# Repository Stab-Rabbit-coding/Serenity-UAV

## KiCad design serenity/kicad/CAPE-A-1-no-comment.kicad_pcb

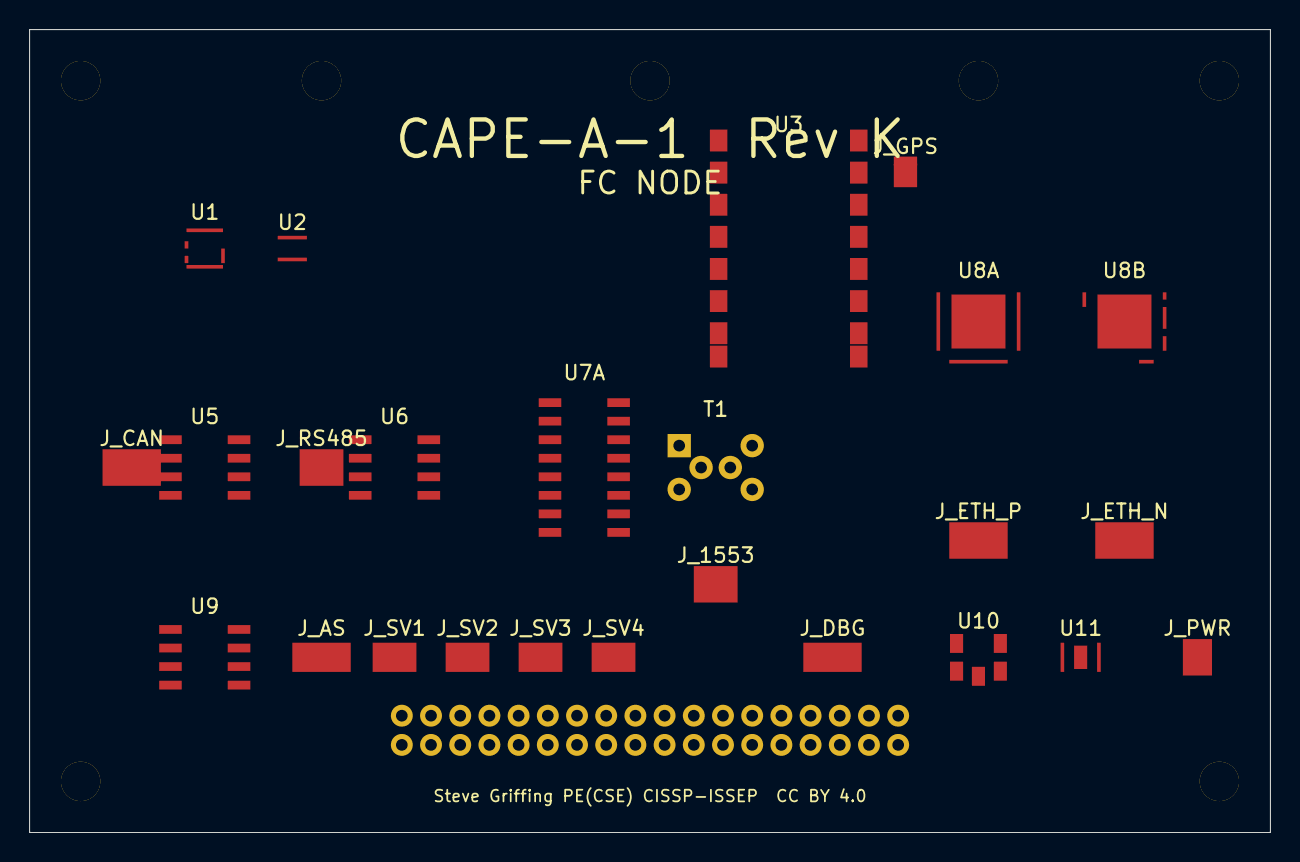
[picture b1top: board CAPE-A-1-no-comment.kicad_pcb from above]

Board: 4 copper layers, 85.0 x 55.0 mm, 25 parts (0 on the bottom side), 25 nets, no tracks yet.

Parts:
J_1553: JST_GH_SM03B-GHS-TB_1x03-1MM_Horizontal
J_AS: JST_SH_SM04B-SRSS-TB_1x04-1MM_Horizontal
J_CAN: JST_GH_SM04B-GHS-TB_1x04-1MM_Horizontal
J_DBG: JST_SH_SM04B-SRSS-TB_1x04-1MM_Horizontal
J_ETH_N: JST_GH_SM04B-GHS-TB_1x04-1MM_Horizontal
J_ETH_P: JST_GH_SM04B-GHS-TB_1x04-1MM_Horizontal
J_GPS: U.FL_Hirose_U.FL-R-SMT-1_Vertical
J_PWR: JST_GH_SM02B-GHS-TB_1x02-1MM_Horizontal
J_RS485: JST_GH_SM03B-GHS-TB_1x03-1MM_Horizontal
J_SV1, J_SV2, J_SV3, J_SV4: JST_SH_SM03B-SRSS-TB_1x03-1MM_Horizontal
T1: PE-68515; Pulse_PE-68515
U1: ICM-42688-P; InvenSense_ICM-42688-P_LGA-14_3x3mm_P0.5mm
U2: BMP388; Bosch_LGA-8_2x2mm_P0.5mm
U3: M10Q; u-blox_MAX-M10Q_LCC-16
U5: ATA6561; SOIC-8_3.9x4.9mm_P1.27mm
U6: MAX3485E; SOIC-8_3.9x4.9mm_P1.27mm
U7A: DS26LV31; SOIC-16_3.9x9.9mm_P1.27mm
U8A, U8B: DP83825I; QFN-32-1EP_5x5mm_P0.5mm_EP3.7x3.7mm
U9: SLB9670; SOIC-8_3.9x4.9mm_P1.27mm
U10: AP2112K-3.3; SOT-25_HandSoldering
U11: TPS62933; WSON-8-1EP_2x2mm_P0.5mm_EP0.9x1.6mm

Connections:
+3V3: J_AS.1, J_CAN.1, J_DBG.4, U1.5, U2.6, U2.8, U3.2, U5.8, U6.8, U7A.4, U7A.8, U7A.12, U7A.16, U8A.24, U8B.24, U9.8, U10.3, U10.5, U11.5, U11.6
+5V: J_PWR.1, J_SV1.1, J_SV2.1, J_SV3.1, J_SV4.1, U11.1, U11.2, U11.8
CANH: J_CAN.2, U5.6
CANL: J_CAN.3, U5.7
ETH_N_RX_N: J_ETH_N.4, U8B.22
ETH_N_RX_P: J_ETH_N.3, U8B.21
ETH_N_TX_N: J_ETH_N.2, U8B.18
ETH_N_TX_P: J_ETH_N.1, U8B.17
ETH_P_RX_N: J_ETH_P.4, U8A.22
ETH_P_RX_P: J_ETH_P.3, U8A.21
ETH_P_TX_N: J_ETH_P.2, U8A.18
ETH_P_TX_P: J_ETH_P.1, U8A.17
GND: J_1553.3, J_AS.2, J_CAN.4, J_DBG.1, J_GPS.2, J_PWR.2, J_RS485.3, J_SV1.2, J_SV2.2, J_SV3.2, J_SV4.2, U1.8, U1.9, U1.10, U1.11, U1.12, U1.14, U2.3, U2.5, U2.7, U3.1, U3.7, U3.8, U3.10, U3.11, U3.13, U3.14, U3.15, U3.16, U5.2, U5.5, U6.4, U7A.3, U7A.7, U7A.11, U7A.15, U8A.19, U8A.23, U8A.33, U8B.33, U9.2, U10.2, U11.3, U11.4, U11.7, U11.9
GPS_ANT_RF: J_GPS.1, U3.9
M1553_RX_N: T1.4, U7A.10
M1553_RX_P: T1.3, U7A.9
M1553_STUB_A: J_1553.1, T1.5
M1553_STUB_B: J_1553.2, T1.6
M1553_TX_N: T1.2, U7A.2
M1553_TX_P: T1.1, U7A.1
RS485_A: J_RS485.1, U6.5, U6.7
RS485_B: J_RS485.2, U6.6
RS485_DE: U6.2, U6.3
VDD_1V8_PHY: U8A.20, U8B.20
VSYS: U10.1, U10.4

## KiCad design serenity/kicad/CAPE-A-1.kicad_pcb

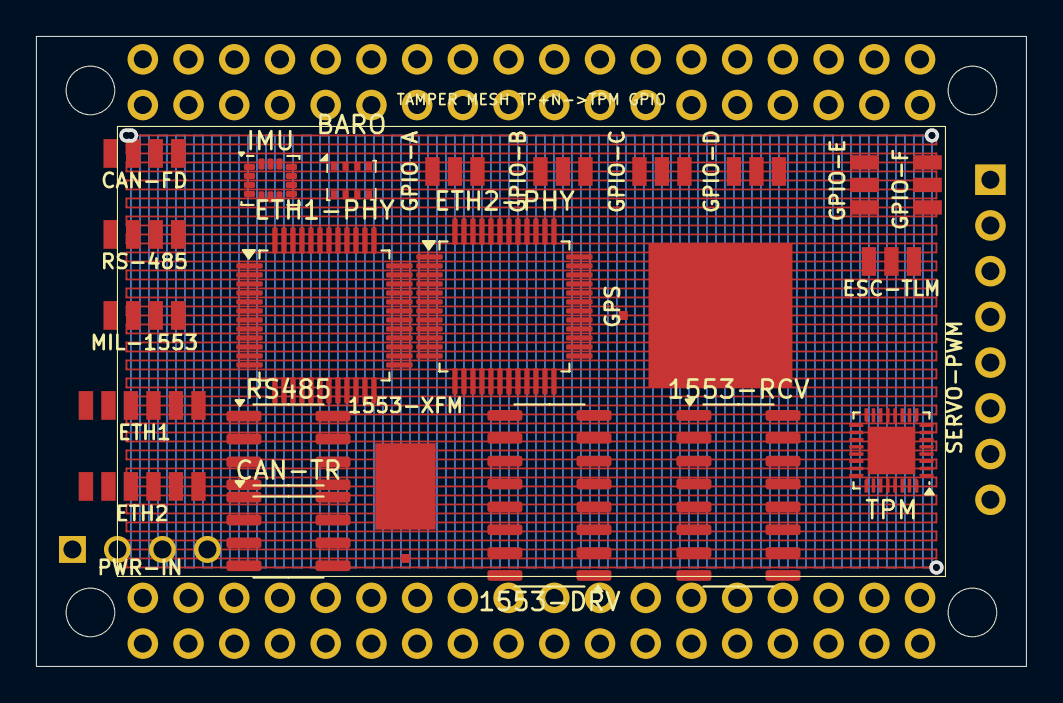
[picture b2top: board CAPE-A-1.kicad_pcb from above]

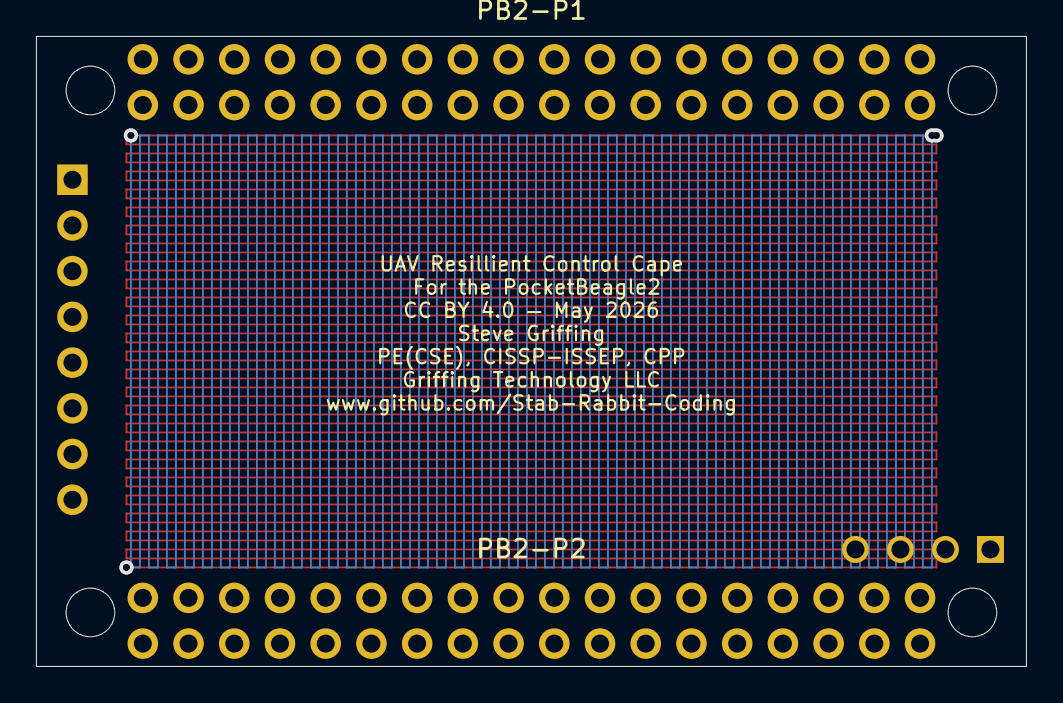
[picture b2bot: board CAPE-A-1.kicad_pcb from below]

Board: 4 copper layers, 55.0 x 35.0 mm, 27 parts (2 on the bottom side), 41 nets.

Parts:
1553-DRV: DS26LV31; SOIC-16_3.9x9.9mm_P1.27mm
1553-RCV: DS26LV32; SOIC-16_3.9x9.9mm_P1.27mm
1553-XFM: SM-1553-11; Package
BARO: BMP388; Bosch_LGA-8_2x2.5mm_P0.65mm_ClockwisePinNumbering
CAN-FD: JST-GH-4P-CAN; JST_GH_4P
CAN-TR: ATA6561; SOIC-8_3.9x4.9mm_P1.27mm
ESC-TLM: JST-GH-3P-ESC-TELEM; JST_GH_3P
ETH1: JST-GH-6P-ETH1; JST_GH_6P
ETH1-PHY, ETH2-PHY: DP83825I; LQFP-48_7x7mm_P0.5mm
ETH2: JST-GH-6P-ETH2; JST_GH_6P
GPIO-A: JST-GH-3P-GPIO; JST_GH_3P_V
GPIO-B: JST-GH-3P-GPIO; JST_GH_3P_V
GPIO-C: JST-GH-3P-GPIO; JST_GH_3P_V
GPIO-D: JST-GH-3P-GPIO; JST_GH_3P_V
GPIO-E: JST-GH-3P-GPIO; JST_GH_3P_V
GPIO-F: JST-GH-3P-GPIO; JST_GH_3P_V
GPS: SAM-M10Q-00B; Package
IMU: ICM-42688-P; LGA-14_3x2.5mm_P0.5mm_LayoutBorder3x4y
MIL-1553: JST-GH-4P-1553; JST_GH_4P
PB2-P1: PB2I-P1-2x18; 2x18_P1_Socket
PB2-P2: PB2I-P2-2x18; 2x18_P2_Socket
PWR-IN: Nano-Fit-4P-POWER; Connector_Molex_NanoFit
RS485: MAX3485E; SOIC-8_3.9x4.9mm_P1.27mm
RS-485: JST-GH-4P-RS485; JST_GH_4P
SERVO-PWM: 1x8-SERVO-PWM; Connector_PinHeader_2.54mm
TPM: SLB9670; QFN-32-1EP_4x4mm_P0.4mm_EP2.65x2.65mm

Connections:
+3V3: PB2-P1.33, PB2-P1.34
+5V: PB2-P1.35, PB2-P2.35
CAN_STB: CAN-TR.1, PB2-P1.14
GND: PB2-P1.1, PB2-P1.2, PB2-P1.36, PB2-P2.36
IMU_INT2: IMU.14, PB2-P1.18
MCAN0_RX: CAN-TR.3, PB2-P1.15
MCAN0_TX: CAN-TR.2, PB2-P1.16
MDC: ETH1-PHY.5, ETH2-PHY.5, PB2-P2.18
MDIO: ETH1-PHY.4, ETH2-PHY.4, PB2-P2.17
PHY1_INTRN: ETH1-PHY.3, PB2-P2.16
PHY1_RSTN: ETH1-PHY.2, PB2-P2.15
PHY2_INTRN: ETH2-PHY.3, PB2-P2.14
PHY2_RSTN: ETH2-PHY.2, PB2-P2.13
PRU_1553_RX_N: 1553-RCV.13, PB2-P1.7
PRU_1553_TX_N: 1553-DRV.6, PB2-P1.9
PRU_1553_TX_P: 1553-DRV.10, PB2-P1.10
RMII0_CRS_DV: ETH1-PHY.29, PB2-P2.29
RMII0_REF_CLK: ETH1-PHY.6, PB2-P2.27
RMII0_RXD1: ETH1-PHY.30, PB2-P2.30
RMII0_RX_ER: ETH1-PHY.28, PB2-P2.28
RMII0_TXD0: ETH1-PHY.37, PB2-P2.34
RMII0_TXD1: ETH1-PHY.32, PB2-P2.33
RMII0_TX_EN: ETH1-PHY.31, PB2-P2.32
RMII1_CRS_DV: ETH2-PHY.29, PB2-P2.21
RMII1_REF_CLK: ETH2-PHY.6, PB2-P2.19
RMII1_RXD1: ETH2-PHY.30, PB2-P2.22
RMII1_RX_ER: ETH2-PHY.28, PB2-P2.20
RMII1_TXD0: ETH2-PHY.37, PB2-P2.26
RMII1_TXD1: ETH2-PHY.32, PB2-P2.25
RMII1_TX_EN: ETH2-PHY.31, PB2-P2.24
RS485_DE: PB2-P1.11, RS485.2, RS485.4
RS485_RX: PB2-P1.12, RS485.5
RS485_TX: PB2-P1.13, RS485.3
SPI0_CLK: BARO.6, IMU.2, PB2-P1.25, TPM.23
SPI0_CS_BARO: BARO.7, PB2-P1.22
SPI0_CS_IMU: IMU.3, PB2-P1.26
SPI0_CS_TPM: PB2-P1.21, TPM.28
SPI0_MISO: BARO.3, IMU.5, PB2-P1.23, TPM.22
SPI0_MOSI: BARO.5, IMU.1, PB2-P1.24, TPM.21
TPM_IRQN: PB2-P2.12, TPM.24
TPM_RSTN: PB2-P2.11, TPM.1

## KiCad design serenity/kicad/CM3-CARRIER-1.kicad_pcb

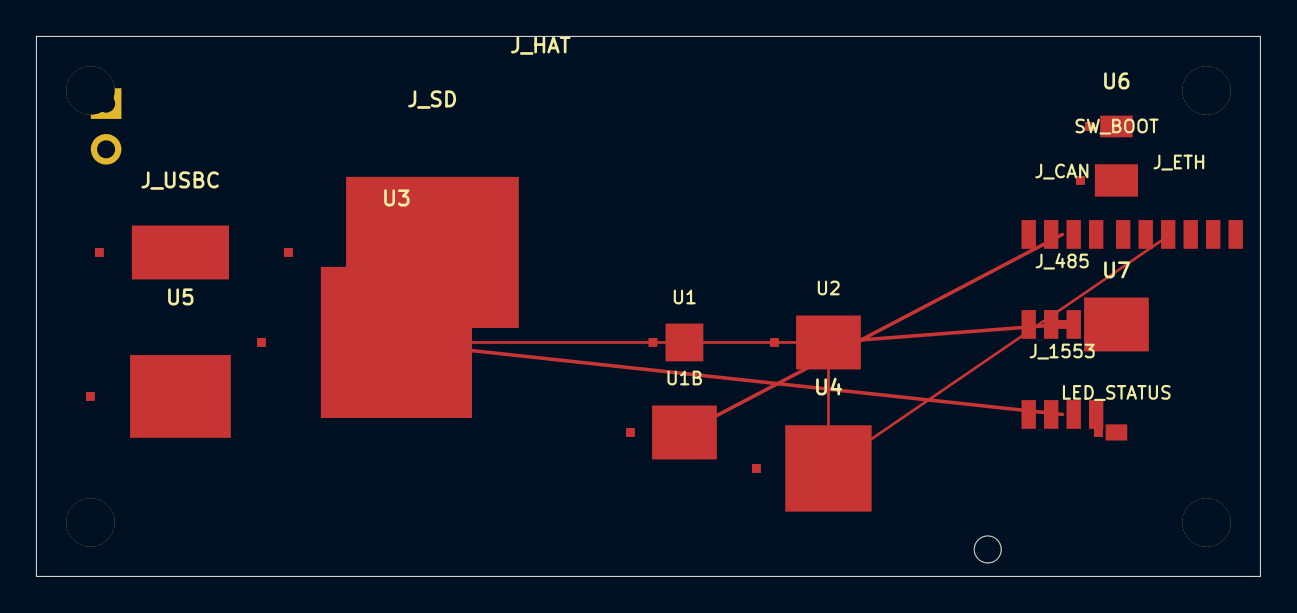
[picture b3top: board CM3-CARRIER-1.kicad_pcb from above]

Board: 4 copper layers, 68.0 x 30.0 mm, 18 parts (1 on the bottom side), 5 nets.

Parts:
J1: SODIMM-200-CM3+; SODIMM_200pin_0.6mm
J_485: JST-GH-4P-485; JST_GH_4P
J_1553: JST-GH-4P-1553; JST_GH_4P
J_CAN: JST-GH-4P-CAN; JST_GH_4P
J_ETH: JST-GH-6P-ETH; JST_GH_6P
J_HAT: HAT-40PIN; PinHeader_2x20_P2.54
J_SD: uSD-OS; Package
J_USBC: USB-C-2.0; Package
LED_STATUS: LED-GRN; Package
SW_BOOT: BOOT-SW; Package
U1: MCP2518FD; Package
U1B: ATA6561; Package
U2: MAX3485E; Package
U3: HI-6130; Package
U4: W5500; Package
U5: CH340C; Package
U6: AP2112K-3.3; Package
U7: CAT24C32; Package

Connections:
+3V3: J_485.2, J_CAN.2, J_ETH.2, U6.EP
+5V: J_USBC.1, U6.1
CANH: J_CAN.3, U1B.1
GND: J_485.1, J_1553.1, J_1553.2, J_CAN.1, J_ETH.1, U1.EP, U1B.EP, U2.EP, U3.EP, U4.EP, U5.EP, U7.EP
SPI0_SCK: J_ETH.3, U1.1, U3.1, U4.1

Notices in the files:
serenity/kicad/CAPE-A-1-no-comment.kicad_pcb:
CC BY 4.0 — creativecommons.org/licenses/by/4.0
Hull: Peter Farell CC BY 4.0 | Nozzle: BamJr CC BY 4.0
Steve Griffing PE(CSE) CISSP-ISSEP  CC BY 4.0
serenity/kicad/CAPE-A-1.kicad_pcb:
Hull: Peter Farell CC BY 4.0 | Nozzle: BamJr CC BY 4.0 | Firefly/Serenity fan-work, not officially licensed
CC BY 4.0 — May 2026
